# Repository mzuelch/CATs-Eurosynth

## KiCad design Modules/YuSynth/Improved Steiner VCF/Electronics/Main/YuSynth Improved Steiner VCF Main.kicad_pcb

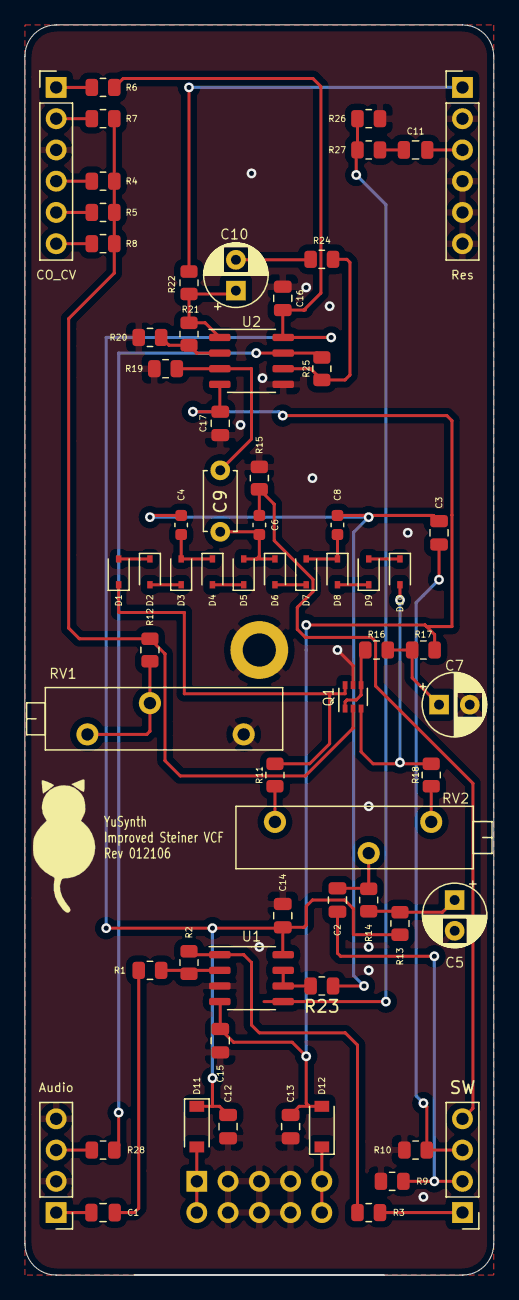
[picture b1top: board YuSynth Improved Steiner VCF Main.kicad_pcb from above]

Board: 2 copper layers, 38.1 x 101.6 mm, 68 parts (1 on the bottom side), 50 nets.

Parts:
C1, C11, C12, C13: 10uF; C_0805_2012Metric
C2, C3: 2.2uF; C_0805_2012Metric
C4, C6, C8: 1.5n; C_0603_1608Metric
C5, C7, C10: 47µF; CP_Radial_D5.0mm_P2.50mm
C9: 680n; C_Disc_D4.7mm_W2.5mm_P5.00mm
C14, C15, C16, C17: 100n; C_0805_2012Metric
D1, D2, D3, D4, D5, D6, D7, D8, D9, D10: 1N4148WS; D_SOD-323
D11, D12: B5819W; D_SOD-123
H1: MountingHole_Pad; MountingHole_2.7mm_M2.5_DIN965_Pad
J1: Power; PinHeader_2x05_P2.54mm_Vertical
J8: Audio; PinHeader_1x04_P2.54mm_Vertical
J9: SW; PinHeader_1x04_P2.54mm_Vertical
J10: CO_CV; PinHeader_1x06_P2.54mm_Vertical
J11: Res; PinHeader_1x06_P2.54mm_Vertical
Q1: BC847BDW1; SOT-363_SC-70-6
R1, R2, R24: 10k; R_0805_2012Metric
R3, R6, R21: 47k; R_0805_2012Metric
R4, R5, R8, R25, R27: 220k; R_0805_2012Metric
R7: 150k; R_0805_2012Metric
R9, R10: 180k; R_0805_2012Metric
R11, R18: 1.8k; R_0805_2012Metric
R12: 220R; R_0805_2012Metric
R13: 390; R_0805_2012Metric
R14, R15, R23, R28: 1k; R_0805_2012Metric
R16, R22: 3.9k; R_0805_2012Metric
R17: 82R; R_0805_2012Metric
R19: 2.2M; R_0805_2012Metric
R20: 22k; R_0805_2012Metric
R26: 1M; R_0805_2012Metric
RV1: 2k; Potentiometer_Bourns_3006P_Horizontal
RV2: 1k; Potentiometer_Bourns_3006P_Horizontal
U1, U2: TL072; SO-8_3.9x4.9mm_P1.27mm

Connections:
+12V: C12.1, C14.1, C16.1, D11.1, R6.2, R13.2, U1.8, U2.8
+12VA: D11.2, J1.1, J1.2
-12V: C13.2, C15.2, C17.2, D12.2, R17.1, U1.4, U2.4
-12VA: D12.1, J1.9, J1.10
AudioIn: C1.2, J8.1
AudioOut: J8.3, R28.2
CO_In: J10.1, R6.1
CO_Out: J10.2, R7.1
CV#1: J10.4, R4.2
CV#2: J10.5, R5.2
GND: C5.2, C7.2, C12.2, C13.1, C14.2, C15.1, C16.2, C17.1, H1.1, J1.3, J1.4, J1.5, J1.6, J1.7, J1.8, J8.2, J8.4, J10.3, J11.2, J11.4, J11.5, J11.6, Q1.5, R9.1, R10.1, R15.1, R19.1, R20.1, R26.1, RV1.1, U1.3, U2.5
unnamed: C1.1, R1.2
unnamed: C2.1, R14.1, RV2.2
unnamed: C3.1, C4.2, C8.2, R23.1
unnamed: C4.1, D3.2, D4.1
unnamed: C5.1, R13.1, R14.2
unnamed: C6.1, C9.2, D5.2, D6.1
unnamed: C7.1, R16.1, R17.2
unnamed: C8.1, D7.2, D8.1
unnamed: C9.1, R19.2, U2.3
unnamed: C10.1, R21.2, R22.2, U2.1
unnamed: C10.2, R24.2
unnamed: C11.2, R27.1
unnamed: D1.1, Q1.6, R11.1
unnamed: D1.2, D2.1
unnamed: D2.2, D3.1
unnamed: D4.2, D5.1
unnamed: D6.2, D7.1
unnamed: D8.2, D9.1
unnamed: D9.2, D10.1
unnamed: D10.2, Q1.3, R18.1
unnamed: Q1.1, Q1.4, R16.2
unnamed: Q1.2, R4.1, R5.1, R7.2, R8.1, R12.2
unnamed: R1.1, R2.2, U1.2
unnamed: R2.1, R3.2, U1.1
unnamed: R11.2, RV2.1
unnamed: R12.1, RV1.2, RV1.3
unnamed: R18.2, RV2.3
unnamed: R20.2, R21.1, U2.2
unnamed: R23.2, U1.6, U1.7
unnamed: R24.1, R25.2, U2.6
unnamed: R25.1, R28.1, U2.7
unnamed: R26.2, R27.2, U1.5
Res_In: J11.1, R22.1
Res_Out: C11.1, J11.3
SW_A: C2.2, J9.2, R9.2
SW_B: C3.2, J9.3, R10.2
SW_C: C6.2, J9.4, R15.2
SW_In: J9.1, R3.1
vOct: J10.6, R8.2
